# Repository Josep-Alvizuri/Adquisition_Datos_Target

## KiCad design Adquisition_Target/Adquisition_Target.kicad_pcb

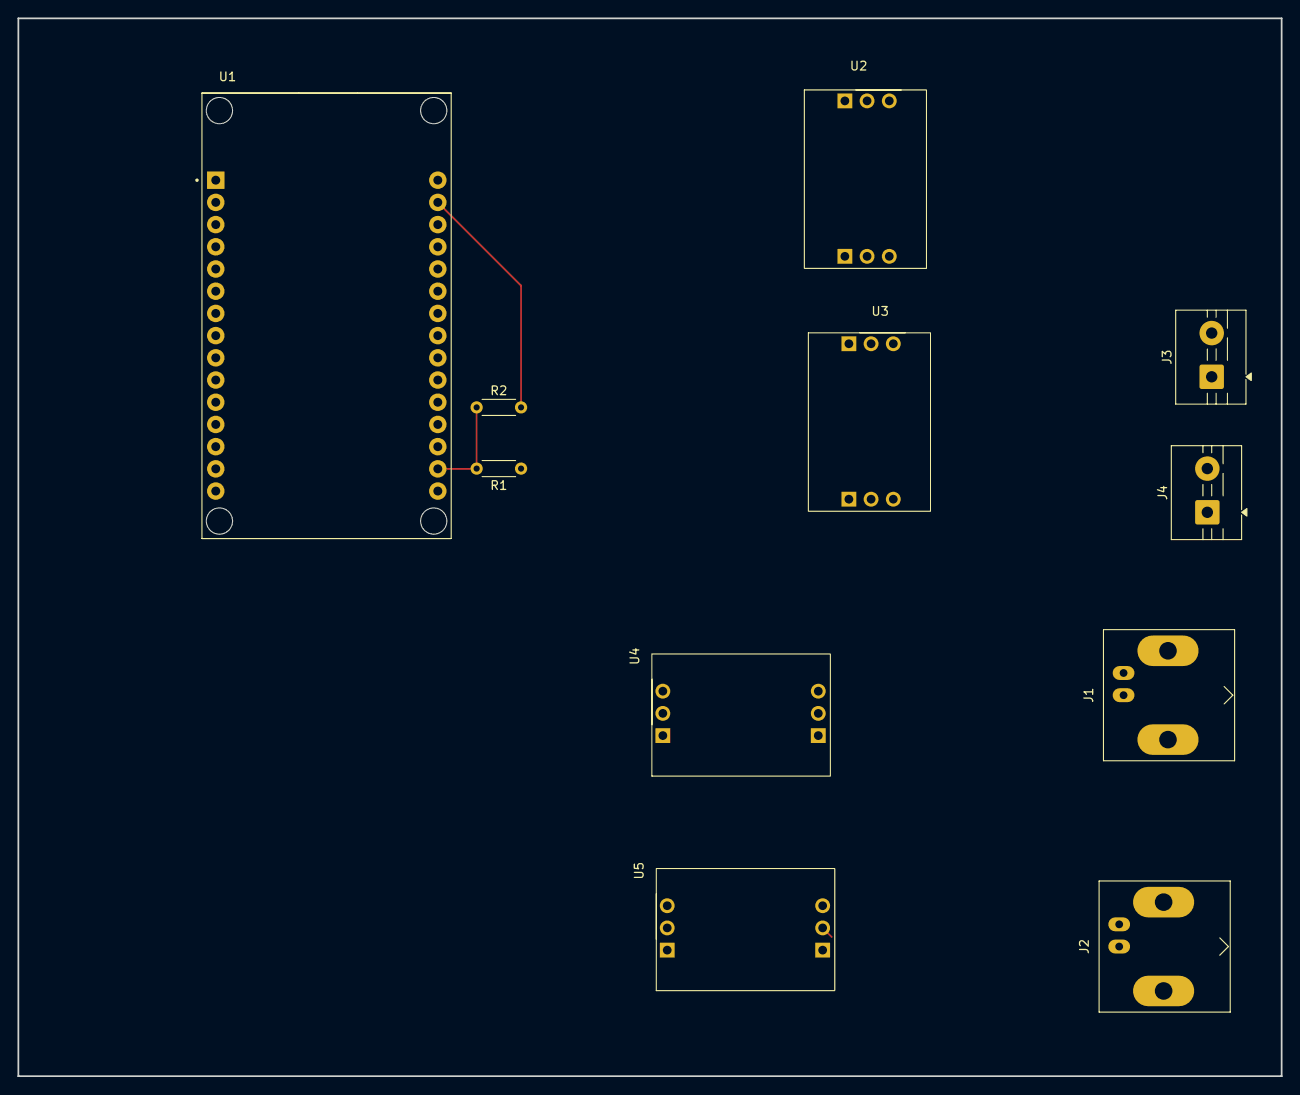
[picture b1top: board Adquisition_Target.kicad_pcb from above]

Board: 2 copper layers, 144.5 x 121.0 mm, 11 parts (0 on the bottom side), 13 nets.

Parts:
J1, J2: Conn_Coaxial; BNC_Amphenol_B6252HB-NPP3G-50_Horizontal
J3, J4: Conn_01x02; TerminalBlock_MaiXu_MX126-5.0-02P_1x02_P5.00mm
R1: 1k; R_Axial_DIN0204_L3.6mm_D1.6mm_P5.08mm_Horizontal
R2: 2k; R_Axial_DIN0204_L3.6mm_D1.6mm_P5.08mm_Horizontal
U1: ESP32-DEVKIT-V1; MODULE_ESP32_DEVKIT_V1
U2, U3, U4, U5: Ezo_sensor

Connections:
/+3V3: U1.1 (3V3), U2.1 (Vcc), U3.1 (Vcc), U4.1 (Vcc), U5.1 (Vcc)
/DO: J1.1 (In), U4.2 (PRB)
/DO-: J1.2 (Ext), U4.3 (PGND)
/SCL: U1.14 (D22), U2.6 (SCL), U3.6 (SCL), U4.6 (SCL), U5.6 (SCL)
/SDA: U1.11 (D21), U2.5 (SDA), U3.5 (SDA), U4.5 (SDA), U5.5 (SDA)
/Sal: J2.1 (In), U5.2 (PRB)
/Sal-: J2.2 (Ext), U5.3 (PGND)
/T+: J4.2, U3.2 (PRB)
/T-: J4.1, U3.3 (PGND)
/pH+: J3.2, U2.2 (PRB)
/pH-: J3.1, U2.3 (PGND)
GND: R2.2, U1.2 (GND), U1.29 (GND), U2.4 (GND), U3.4 (GND), U4.4 (GND), U5.4 (GND)
unnamed: R1.2, R2.1, U1.17 (VP)

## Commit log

2026-02-17 cambio de raiz
